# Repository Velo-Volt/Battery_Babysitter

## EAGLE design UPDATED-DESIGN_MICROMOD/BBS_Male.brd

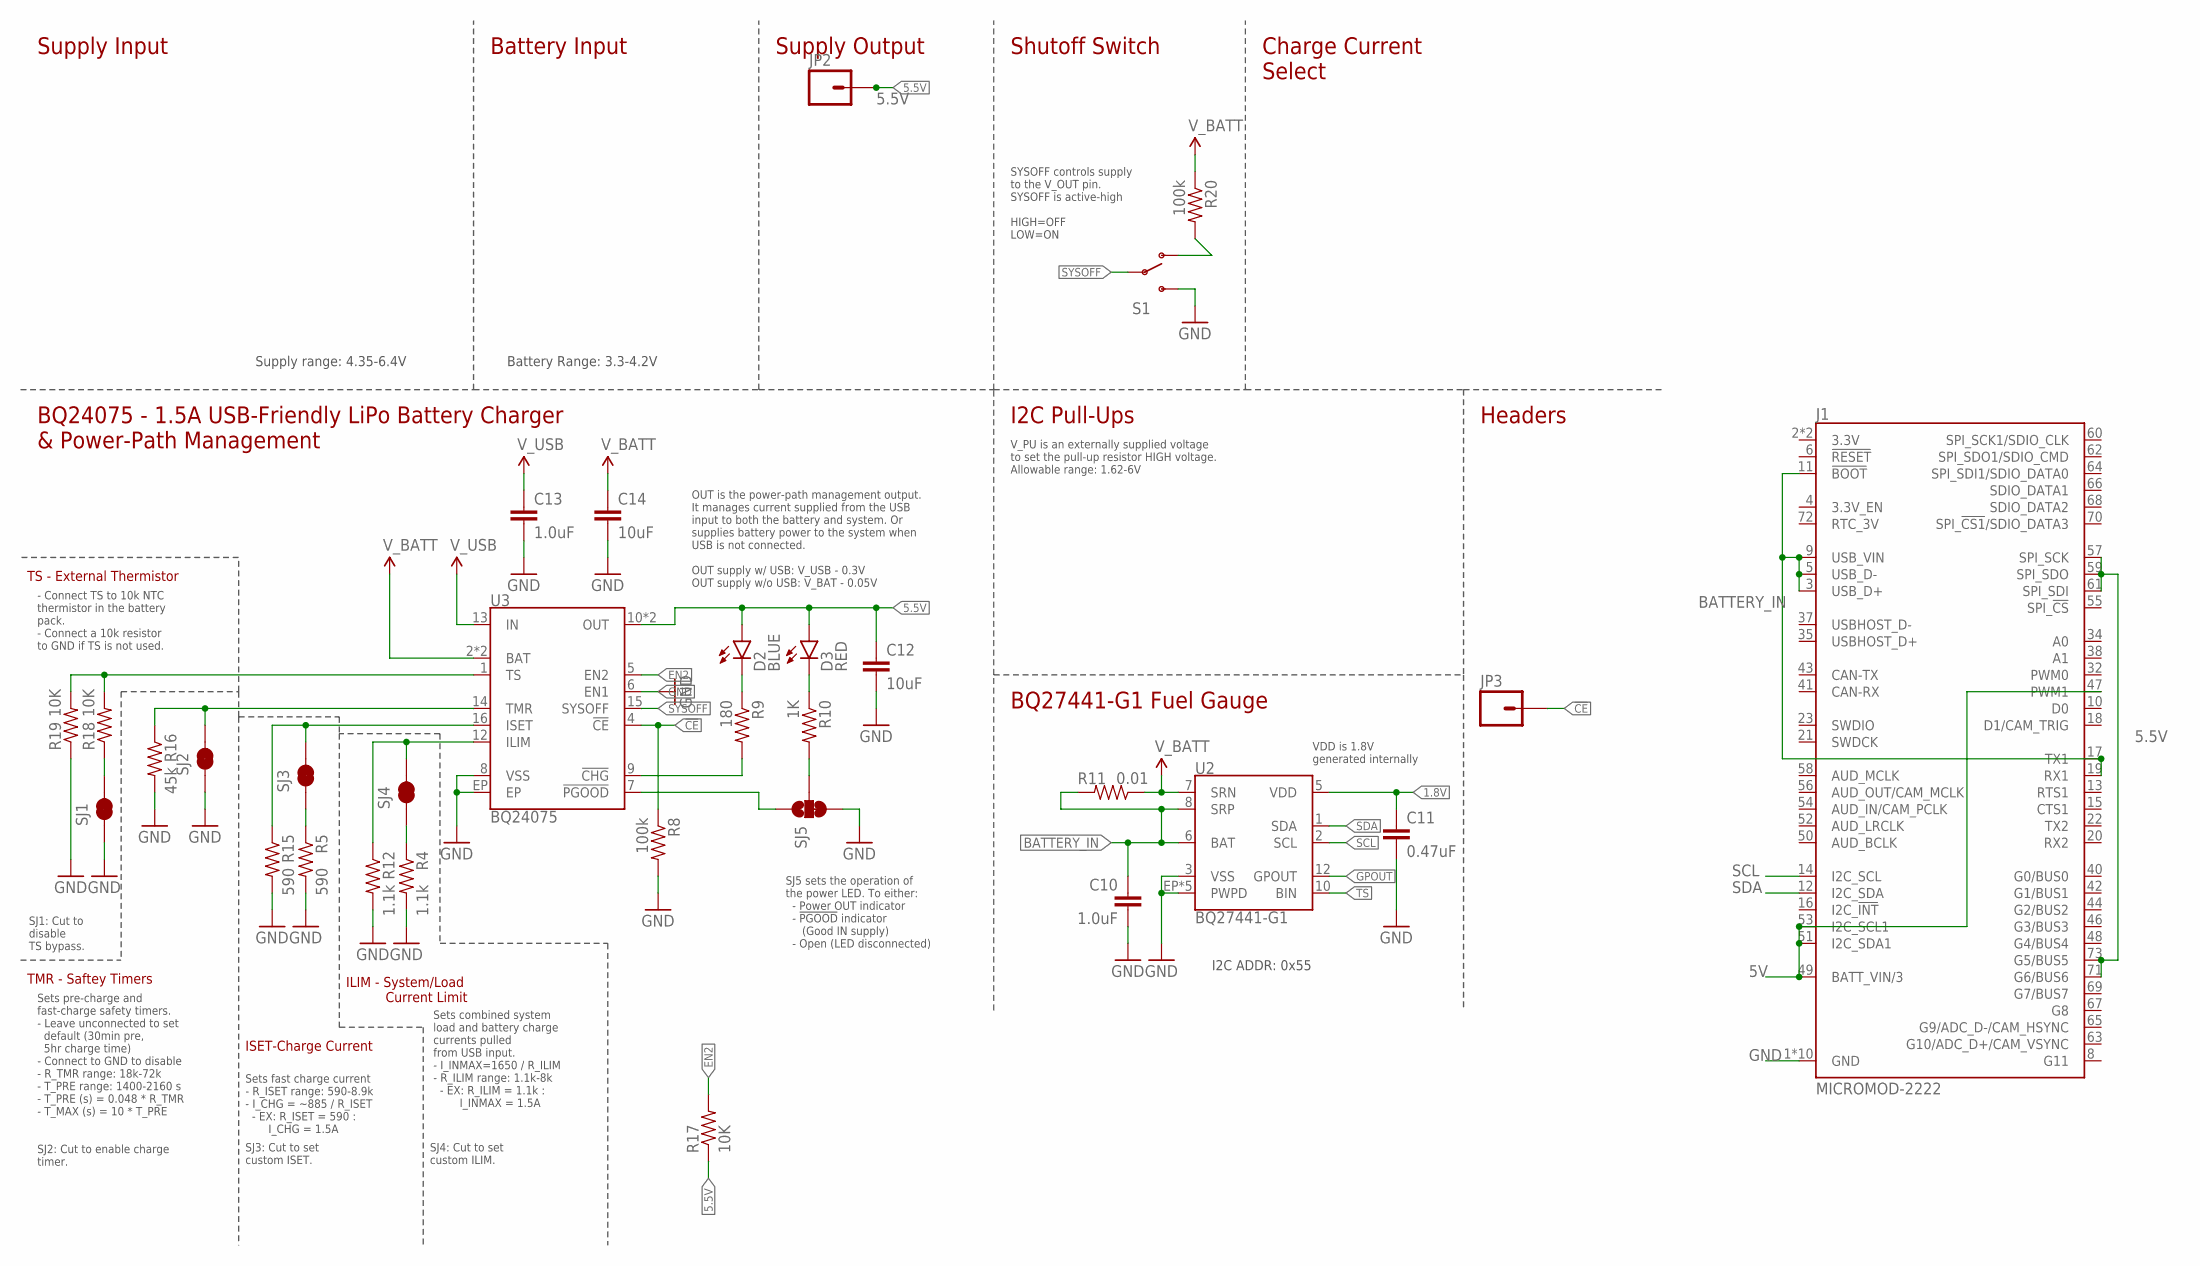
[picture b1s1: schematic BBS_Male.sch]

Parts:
C10: 1.0uF; 0603-CAP
C11: 0.47uF; 0603-CAP
C12, C14: 10uF; 0805-CAP
C13: 1.0uF; 1206-CAP
D2: BLUE; LED-0603
D3: RED; LED-0603
J1: MICROMOD-2222; M.2-CARD-E-22
JP2, JP3: M01PTH_NO_SILK_YES_STOP; 1X01_NO_SILK
R4, R12: 1.1k; 0603-RES
R5, R15: 590; 0603-RES
R8, R20: 100k; 0603-RES
R9: 180; 0603-RES
R10: 1K; 0603-RES
R11: 0.01; 1206
R16: 45k; 0603-RES
R17, R18, R19: 10K; 0603-RES
S1: SWITCH-SPDT-SMD-A; SWITCH-SPST-SMD-A
SJ1, SJ2, SJ3, SJ4: JUMPER-PAD-2-NC_BY_TRACE; PAD-JUMPER-2-NC_BY_TRACE_YES_SILK
SJ5: JUMPER-PAD-3-2OF3_NC_BY_TRACE_SMALL; PAD-JUMPER-3-2OF3_NC_BY_TRACE_YES_SILK_FULL_BOX
U2: BQ27441-G1; PDSO-N12
U3: BQ24075; PVQFN-N16

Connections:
1.8V: C11.1, U2.5 (VDD)
5.5V: C12.1, D2.A, D3.A, J1.57 (SPI_SCK), J1.59 (SPI_SDO), J1.61 (SPI_SDI), J1.71 (G6/BUS6), J1.73 (G5/BUS5), JP2.1, R17.1, U3.10 (OUT), U3.11 (OUT)
5V: C13.1, J1.47 (PWM1), J1.49 (BATT_VIN/3), J1.51 (I2C_SDA1), J1.53 (I2C_SCL1), U3.13 (IN)
!CE!: JP3.1, R8.1, U3.4 (!CE!)
!CHG!: R9.2, U3.9 (!CHG!)
!PGOOD!: SJ5.1, U3.7 (!PGOOD!)
BATTERY_IN: C10.1, J1.3 (USB_D+), J1.5 (USB_D-), J1.9 (USB_VIN), J1.11 (!BOOT!), J1.17 (TX1), J1.19 (RX1), R11.2, U2.6 (BAT), U2.8 (SRP)
EN2: R17.2, U3.5 (EN2)
GND: C10.2, C11.2, C12.2, C13.2, C14.2, J1.1 (GND), J1.7 (GND), J1.33 (GND), J1.36 (GND), J1.39 (GND), J1.45 (GND), J1.75 (GND), J1.GND1 (GND), J1.GND2 (GND), J1.GND3 (GND), R4.2, R5.2, R8.2, R12.2, R15.2, R16.2, R19.1, S1.3 (S), SJ1.1, SJ2.1, SJ5.3, U2.3 (VSS), U2.EP (PWPD), U2.EP1 (PWPD), U2.EP2 (PWPD), U2.EP3 (PWPD), U2.EP4 (PWPD), U3.6 (EN1), U3.8 (VSS), U3.EP
GPOUT: U2.12 (GPOUT)
ILIM: R12.1, SJ4.2, U3.12 (ILIM)
ISET: R15.1, SJ3.2, U3.16 (ISET)
unnamed: R18.1, SJ1.2
unnamed: R20.2, S1.1 (O)
unnamed: R4.1, SJ4.1
unnamed: R5.1, SJ3.1
unnamed: R10.2, SJ5.2
unnamed: D2.C, R9.1
unnamed: D3.C, R10.1
SCL: J1.14 (I2C_SCL), U2.2 (SCL)
SDA: J1.12 (I2C_SDA), U2.1 (SDA)
SYSOFF: S1.2, U3.15 (SYSOFF)
TMR: R16.1, SJ2.2, U3.14 (TMR)
TS: R18.2, R19.2, U2.10 (BIN), U3.1 (TS)
V_BATT: C14.1, R11.1, R20.1, U2.7 (SRN), U3.2 (BAT), U3.3 (BAT)

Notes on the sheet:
Sets fast charge current - R_ISET range: 590-8.9k - I_CHG = ~885 / R_ISET - EX: R_ISET = 590 : I_CHG = 1.5A
Sets combined system load and battery charge currents pulled from USB input. - I_INMAX=1650 / R_ILIM - R_ILIM range: 1.1k-8k - EX: R_ILIM = 1.1k : I_INMAX = 1.5A
Supply Input
Battery Input
Supply Output
Shutoff Switch
Charge Current Select
BQ24075 - 1.5A USB-Friendly LiPo Battery Charger & Power-Path Management
I2C Pull-Ups
BQ27441-G1 Fuel Gauge
Headers
SYSOFF controls supply to the V_OUT pin. SYSOFF is active-high HIGH=OFF LOW=ON
SJ1: Cut to disable TS bypass.
SJ3: Cut to set custom ISET.
SJ4: Cut to set custom ILIM.
ILIM - System/Load Current Limit
ISET-Charge Current
TMR - Saftey Timers
Sets pre-charge and fast-charge safety timers. - Leave unconnected to set default (30min pre, 5hr charge time) - Connect to GND to disable - R_TMR range: 18k-72k - T_PRE range: 1400-2160 s - T_PRE (s) = 0.048 * R_TMR - T_MAX (s) = 10 * T_PRE
SJ2: Cut to enable charge timer.
TS - External Thermistor
- Connect TS to 10k NTC thermistor in the battery pack. - Connect a 10k resistor to GND if TS is not used.
V_PU is an externally supplied voltage to set the pull-up resistor HIGH voltage. Allowable range: 1.62-6V
Supply range: 4.35-6.4V
VDD is 1.8V generated internally
OUT is the power-path management output. It manages current supplied from the USB input to both the battery and system. Or supplies battery power to the system when USB is not connected. OUT supply w/ USB: V_USB - 0.3V OUT supply w/o USB: V_BAT - 0.05V
I2C ADDR: 0x55
SJ5 sets the operation of the power LED. To either: - Power OUT indicator - !PGOOD! indicator (Good IN supply) - Open (LED disconnected)
Battery Range: 3.3-4.2V

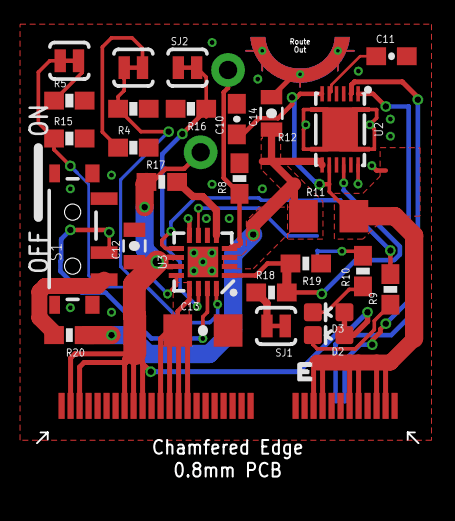
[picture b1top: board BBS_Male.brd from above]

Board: 2 copper layers, 21.2 x 24.8 mm, 31 parts (1 on the bottom side), 24 nets.

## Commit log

2021-01-27 Create CHEKED ...

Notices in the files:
parts and their libraries:
SparkFun-Capacitors: Licensing: Creative Commons ShareAlike 4.0 International - https://creativecommons.org/licenses/by-sa/4.0
